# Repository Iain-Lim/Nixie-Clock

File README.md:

## Nixie_ver1
- The first board which house all the nixie tubes and the driver for it.

## Nixie2nd_ver1
- The second board which house the Arduino Nano, High Voltage Power Supply, Real-time clock, and other components
- Do note that there is a missing connection for the arduino to the ground.

## divergence_meter_ver_1_4
- Functional code for the clock/divergence meter.
- Yet to implement rolling numbers for the divegence number.

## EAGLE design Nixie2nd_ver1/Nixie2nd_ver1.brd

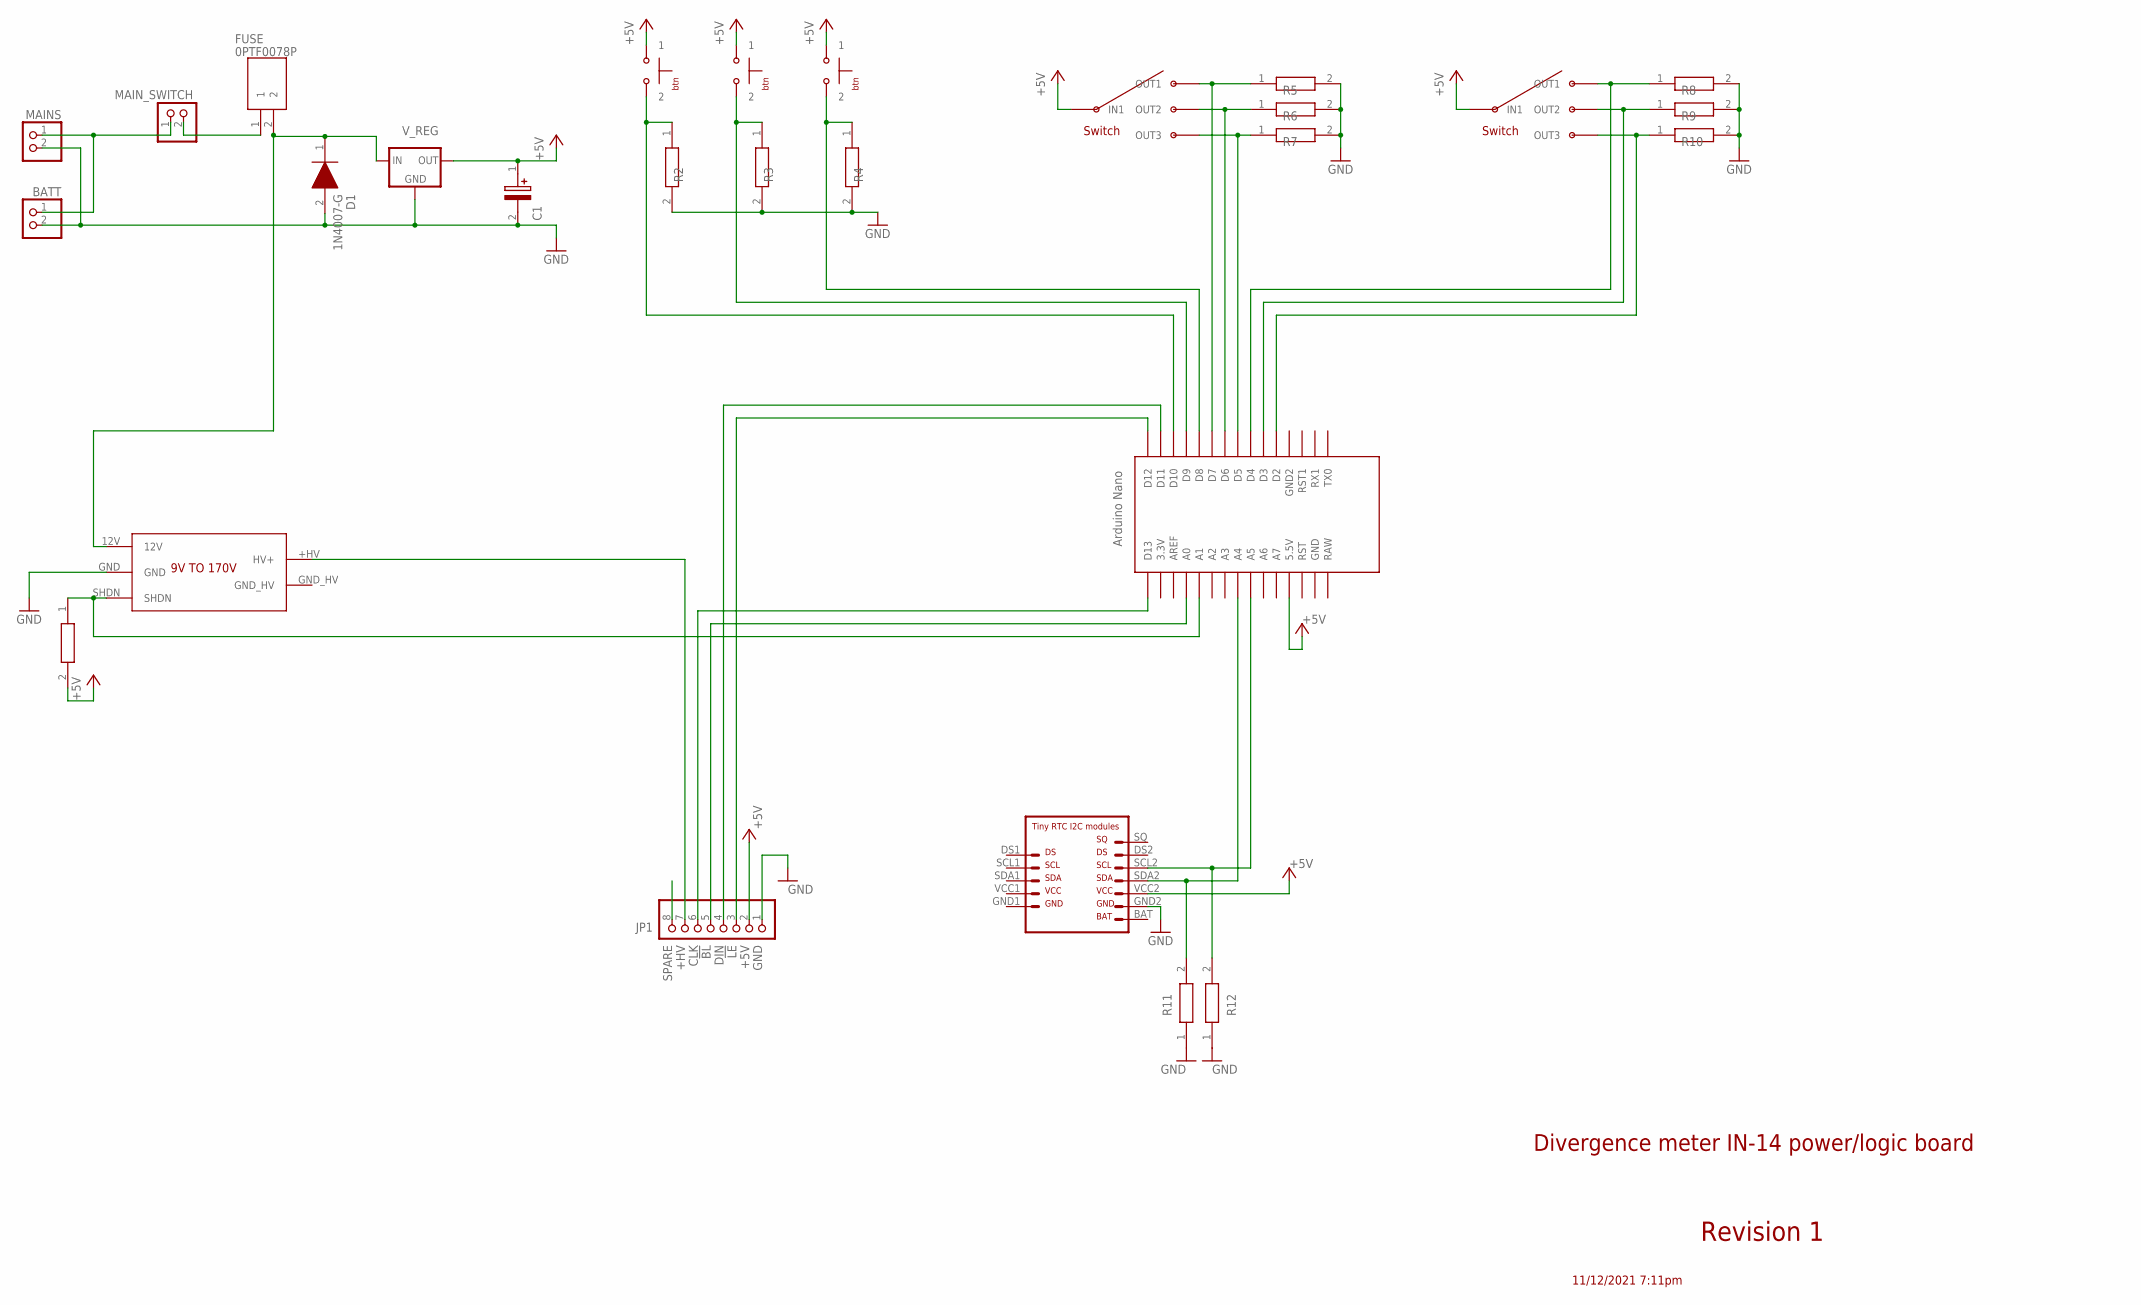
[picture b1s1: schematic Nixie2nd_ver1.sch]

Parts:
BATT: PINHD-1X2; 1X02
BTN_1, BTN_2, BTN_3: PUSH_BTN
C1: ESMG250ELL330ME11D; CAPPRD275W60D825H1300
D1: 1N4007-G; DIOAD1410W90L470D235
FUSE: 0PTF0078P
JP1: PINHD-1X8; 1X08
MAINS: PINHD-1X2; 1X02
MAIN_SWITCH: PINHD-1X2; 1X02
R1, R2, R3, R4, R5, R6, R7, R8, R9, R10, R11, R12: CR0805-FX-3303ELF; RESC2012X60N
SWITCH_1, SWITCH_2: 3WAY_SWITCH
U$1: NANO
U$2: VOLTAGE_9TO170VOLT_9TO170; VOLTAGE_9TO170
U$3: RTC
V_REG: 78XXS

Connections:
!BL: JP1.5, U$1.A0
!LE: JP1.3, U$1.D12
+5V: BTN_1.1, BTN_2.1, BTN_3.1, C1.1 (+), JP1.2, R1.2, SWITCH_1.IN1, SWITCH_2.IN1, U$1.5V (5.5V), U$3.VCC2, V_REG.OUT
+HV: JP1.7, U$2.+HV (HV+)
CLK: JP1.6, U$1.D13
DIN: JP1.4, U$1.D11
GND: BATT.2, C1.2 (-), D1.2 (A), JP1.1, MAINS.2, R2.2, R3.2, R4.2, R5.2, R6.2, R7.2, R8.2, R9.2, R10.2, R11.1, R12.1, U$2.GND, U$3.GND2, V_REG.GND
MAINS: BATT.1, MAINS.1, MAIN_SWITCH.1
MAINS_REG: D1.1 (K), FUSE.2, U$2.12V, V_REG.IN
unnamed: R5.1, SWITCH_1.OUT1, U$1.D7
unnamed: R6.1, SWITCH_1.OUT2, U$1.D6
unnamed: R7.1, SWITCH_1.OU3 (OUT3), U$1.D5
unnamed: R8.1, SWITCH_2.OUT1, U$1.D4
unnamed: R9.1, SWITCH_2.OUT2, U$1.D3
unnamed: R10.1, SWITCH_2.OU3 (OUT3), U$1.D2
unnamed: BTN_3.2, R4.1, U$1.D8
unnamed: BTN_2.2, R3.1, U$1.D9
unnamed: BTN_1.2, R2.1, U$1.D10
unnamed: FUSE.1, MAIN_SWITCH.2
SCL: R12.2, U$1.A5, U$3.SCL2
SDA: R11.2, U$1.A4, U$3.SDA2
SHDN: R1.1, U$1.A1, U$2.SHDN
SPARE: JP1.8

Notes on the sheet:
Divergence meter IN-14 power/logic board
11/12/2021 7:11pm
Revision 1

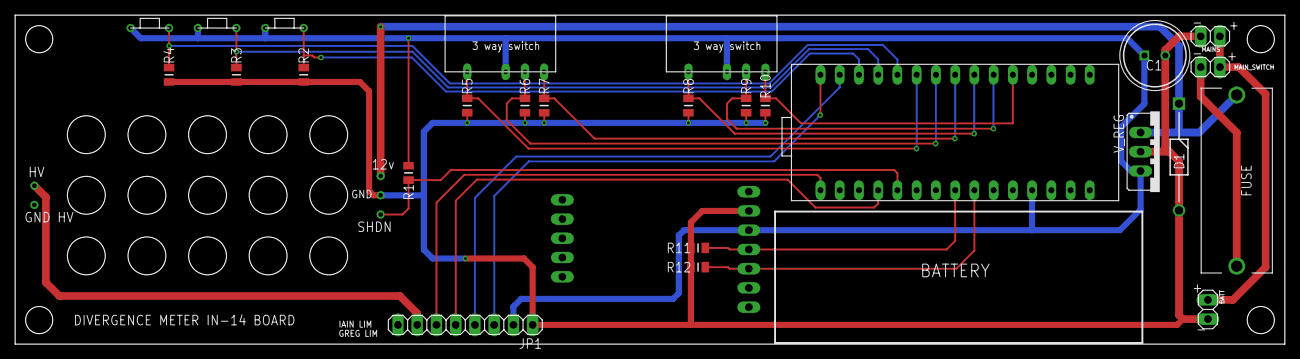
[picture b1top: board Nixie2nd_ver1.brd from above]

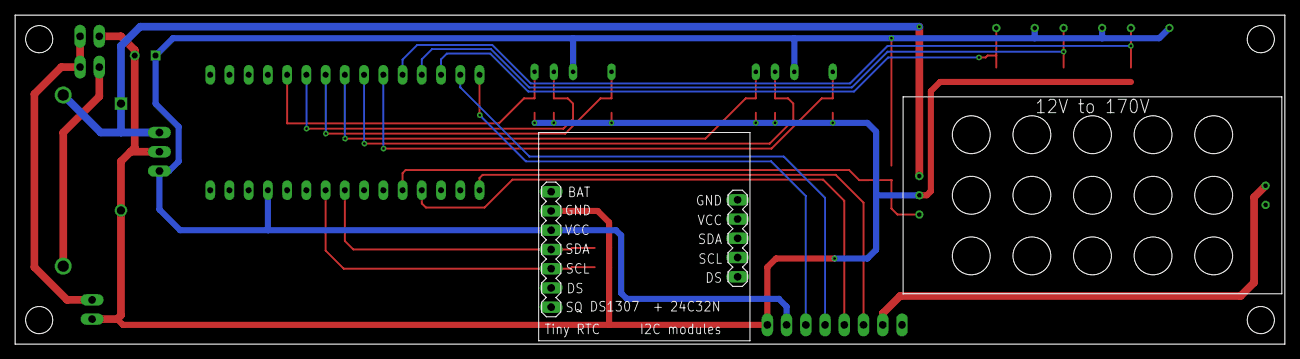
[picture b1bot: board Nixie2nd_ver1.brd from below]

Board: 2 copper layers, 167.6 x 43.4 mm, 28 parts (2 on the bottom side), 22 nets.

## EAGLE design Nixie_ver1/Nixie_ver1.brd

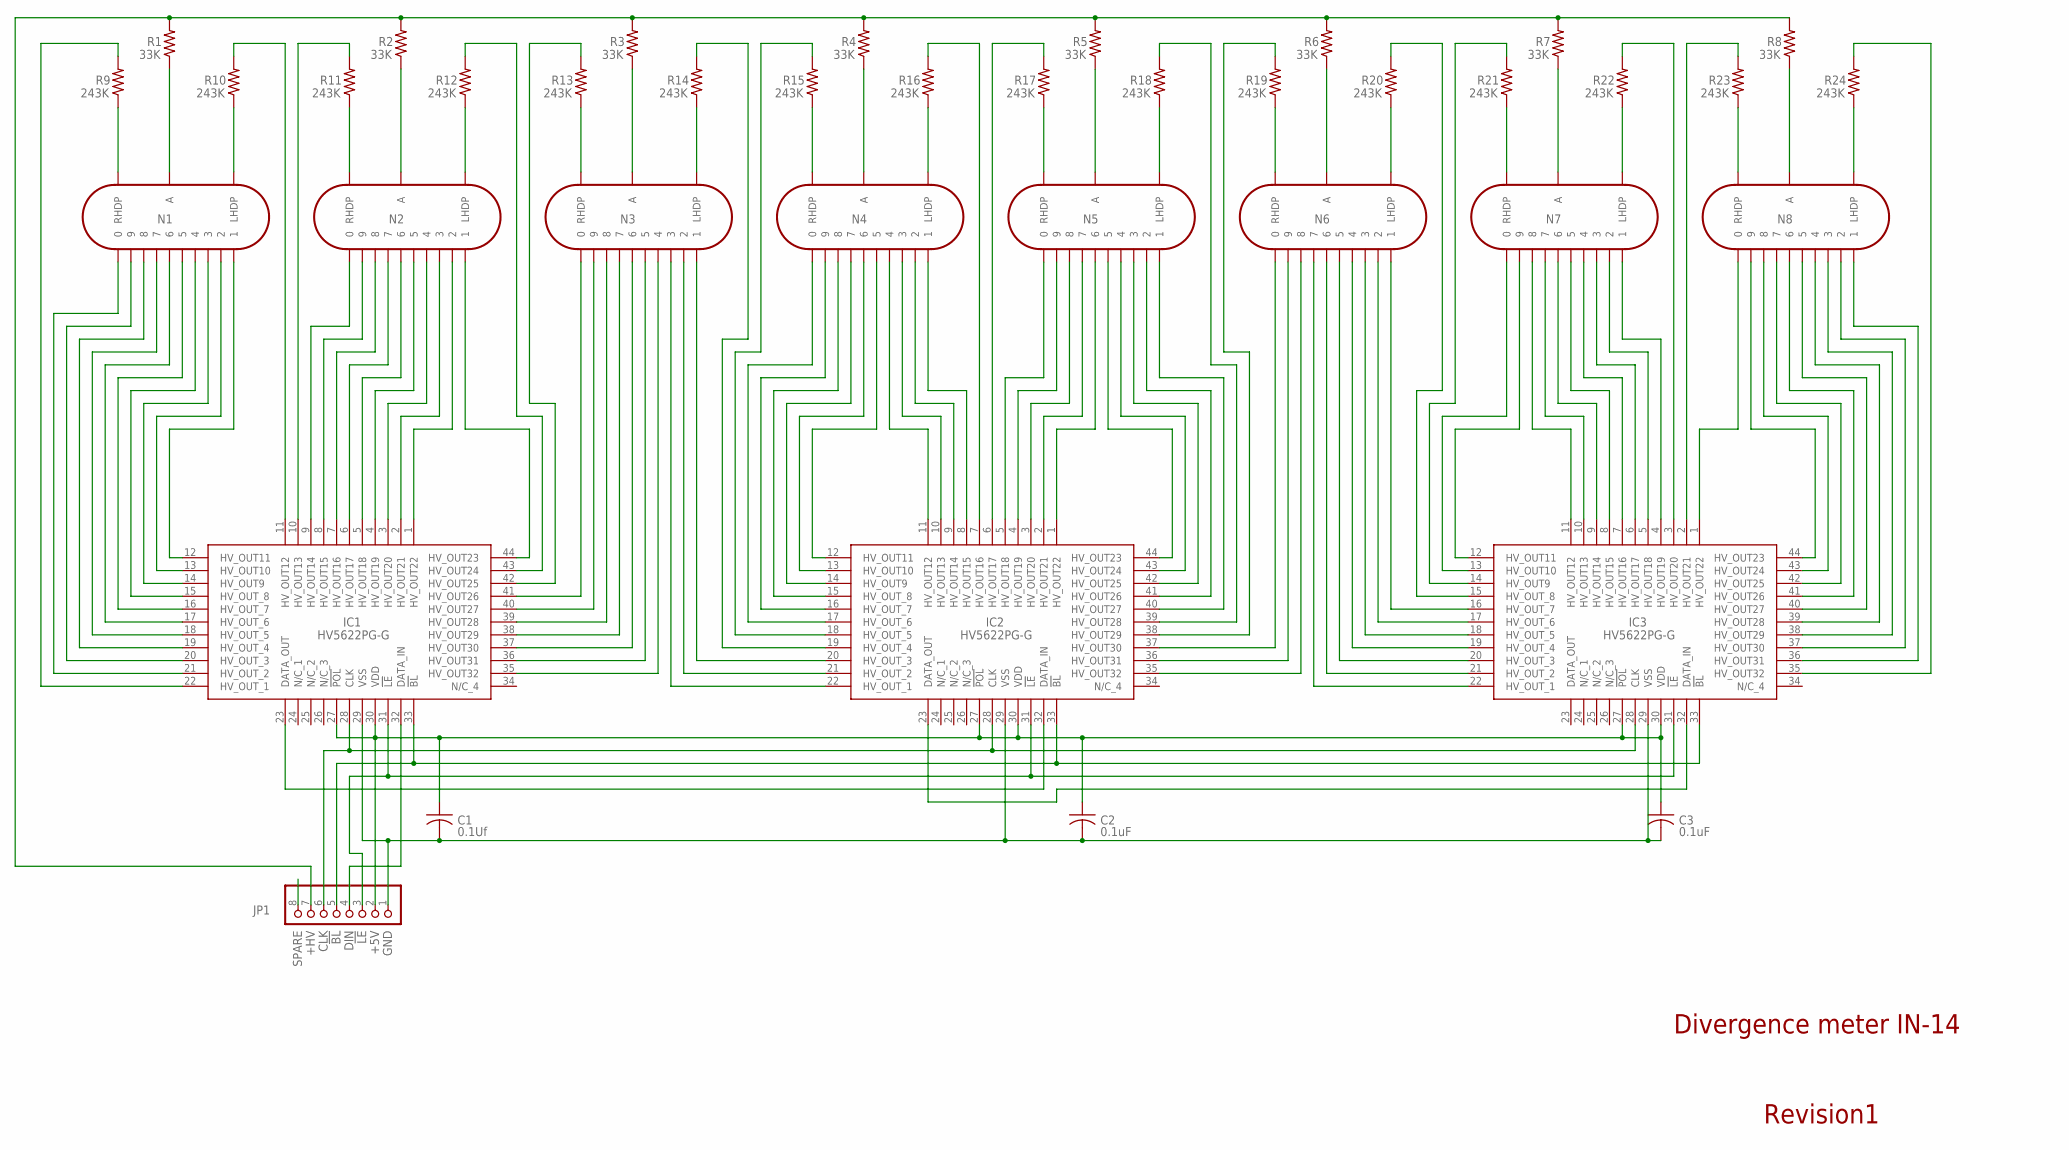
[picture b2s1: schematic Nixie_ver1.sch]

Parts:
C1: 0.1Uf; C025-024X044
C2, C3: 0.1uF; C025-024X044
IC1, IC2, IC3: HV5622PG-G; QFP80P1390X1390X235-44N
JP1: PINHD-1X8; 1X08
N1, N2, N3, N4, N5, N6, N7, N8: IN-14
R1, R2, R3, R4, R5, R6, R7, R8: 33K; 0204/7
R9, R10, R11, R12, R13, R14, R15, R16, R17, R18, R19, R20, R21, R22, R23, R24: 243K; 0204/7

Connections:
!BL!: IC1.33 (!BL), IC2.33 (!BL), IC3.33 (!BL), JP1.5
!LE!: IC1.31 (!LE), IC2.31 (!LE), IC3.31 (!LE), JP1.3
+5V: C1.1, C2.1, C3.1, IC1.27 (!POL), IC1.30 (VDD), IC2.27 (!POL), IC2.30 (VDD), IC3.27 (!POL), IC3.30 (VDD), JP1.2
+HV: JP1.7, R1.2, R2.2, R3.2, R4.2, R5.2, R6.2, R7.2, R8.2
CLK: IC1.28 (CLK), IC2.28 (CLK), IC3.28 (CLK), JP1.6
DIN: IC1.32 (DATA_IN), JP1.4
GND: C1.2, C2.2, C3.2, IC1.29 (VSS), IC2.29 (VSS), IC3.29 (VSS), JP1.1
unnamed: IC1.23 (DATA_OUT), IC2.32 (DATA_IN)
unnamed: IC2.23 (DATA_OUT), IC3.32 (DATA_IN)
unnamed: IC1.11 (HV_OUT12), R10.2
unnamed: IC1.13 (HV_OUT10), N1.2
unnamed: IC1.14 (HV_OUT9), N1.3
unnamed: IC1.15 (HV_OUT_8), N1.4
unnamed: IC1.16 (HV_OUT_7), N1.5
unnamed: IC1.17 (HV_OUT_6), N1.6
unnamed: IC1.18 (HV_OUT_5), N1.7
unnamed: IC1.19 (HV_OUT_4), N1.8
unnamed: IC1.20 (HV_OUT_3), N1.9
unnamed: IC1.12 (HV_OUT11), N1.1
unnamed: IC1.21 (HV_OUT_2), N1.0
unnamed: IC1.22 (HV_OUT_1), R9.2
unnamed: N1.RHDP, R9.1
unnamed: N1.LHDP, R10.1
unnamed: IC1.10 (HV_OUT13), R11.2
unnamed: N1.A, R1.1
unnamed: N2.RHDP, R11.1
unnamed: N2.A, R2.1
unnamed: N2.LHDP, R12.1
unnamed: IC1.9 (HV_OUT14), N2.0
unnamed: IC1.8 (HV_OUT15), N2.9
unnamed: IC1.7 (HV_OUT16), N2.8
unnamed: IC1.6 (HV_OUT17), N2.7
unnamed: IC1.5 (HV_OUT18), N2.6
unnamed: IC1.4 (HV_OUT19), N2.5
unnamed: IC1.3 (HV_OUT20), N2.4
unnamed: IC1.2 (HV_OUT21), N2.3
unnamed: IC1.1 (HV_OUT22), N2.2
unnamed: IC1.44 (HV_OUT23), N2.1
unnamed: IC1.43 (HV_OUT24), R12.2
unnamed: IC1.42 (HV_OUT25), R13.2
unnamed: N3.RHDP, R13.1
unnamed: N3.A, R3.1
unnamed: N3.LHDP, R14.1
unnamed: IC1.41 (HV_OUT26), N3.0
unnamed: IC1.40 (HV_OUT27), N3.9
unnamed: IC1.39 (HV_OUT28), N3.8
unnamed: IC1.38 (HV_OUT29), N3.7
unnamed: IC1.37 (HV_OUT30), N3.6
unnamed: IC1.36 (HV_OUT31), N3.5
unnamed: IC1.35 (HV_OUT32), N3.4
unnamed: IC2.22 (HV_OUT_1), N3.3
unnamed: IC2.21 (HV_OUT_2), N3.2
unnamed: IC2.20 (HV_OUT_3), N3.1
unnamed: IC2.19 (HV_OUT_4), R14.2
unnamed: IC2.18 (HV_OUT_5), R15.2
unnamed: N4.RHDP, R15.1
unnamed: N4.A, R4.1
unnamed: N4.LHDP, R16.1
unnamed: IC2.17 (HV_OUT_6), N4.0
unnamed: IC2.16 (HV_OUT_7), N4.9
unnamed: IC2.15 (HV_OUT_8), N4.8
unnamed: IC2.14 (HV_OUT9), N4.7
unnamed: IC2.13 (HV_OUT10), N4.6
unnamed: IC2.1 (HV_OUT22), N5.6
unnamed: IC2.11 (HV_OUT12), N4.4
unnamed: IC2.10 (HV_OUT13), N4.3
unnamed: IC2.9 (HV_OUT14), N4.2
unnamed: IC2.8 (HV_OUT15), N4.1
unnamed: IC2.7 (HV_OUT16), R16.2
unnamed: IC2.6 (HV_OUT17), R17.2
unnamed: N5.RHDP, R17.1
unnamed: N5.A, R5.1
unnamed: N5.LHDP, R18.1
unnamed: IC2.5 (HV_OUT18), N5.0
unnamed: IC2.4 (HV_OUT19), N5.9
unnamed: IC2.3 (HV_OUT20), N5.8
unnamed: IC2.2 (HV_OUT21), N5.7
unnamed: N6.RHDP, R19.1
unnamed: IC2.44 (HV_OUT23), N5.5
unnamed: IC2.43 (HV_OUT24), N5.4
unnamed: IC2.42 (HV_OUT25), N5.3
unnamed: IC2.41 (HV_OUT26), N5.2
unnamed: IC2.40 (HV_OUT27), N5.1
unnamed: IC2.39 (HV_OUT28), R18.2
unnamed: IC2.38 (HV_OUT29), R19.2
unnamed: IC2.12 (HV_OUT11), N4.5
unnamed: N6.A, R6.1
unnamed: N6.LHDP, R20.1
unnamed: N7.RHDP, R21.1
unnamed: N7.A, R7.1
unnamed: N7.LHDP, R22.1
unnamed: N8.RHDP, R23.1
unnamed: N8.A, R8.1
unnamed: N8.LHDP, R24.1
unnamed: IC2.37 (HV_OUT30), N6.0
unnamed: IC2.36 (HV_OUT31), N6.9
unnamed: IC2.35 (HV_OUT32), N6.8
unnamed: IC3.22 (HV_OUT_1), N6.7
unnamed: IC3.21 (HV_OUT_2), N6.6
unnamed: IC3.20 (HV_OUT_3), N6.5
unnamed: IC3.19 (HV_OUT_4), N6.4
unnamed: IC3.18 (HV_OUT_5), N6.3
unnamed: IC3.17 (HV_OUT_6), N6.2
unnamed: IC3.16 (HV_OUT_7), N6.1
unnamed: IC3.15 (HV_OUT_8), R20.2
unnamed: IC3.14 (HV_OUT9), R21.2
unnamed: IC3.13 (HV_OUT10), N7.0
unnamed: IC3.12 (HV_OUT11), N7.9
unnamed: IC3.11 (HV_OUT12), N7.8
unnamed: IC3.10 (HV_OUT13), N7.7
unnamed: IC3.9 (HV_OUT14), N7.6
unnamed: IC3.8 (HV_OUT15), N7.5
unnamed: IC3.7 (HV_OUT16), N7.4
unnamed: IC3.6 (HV_OUT17), N7.3
unnamed: IC3.5 (HV_OUT18), N7.2
unnamed: IC3.4 (HV_OUT19), N7.1
unnamed: IC3.3 (HV_OUT20), R22.2
unnamed: IC3.2 (HV_OUT21), R23.2
unnamed: IC3.1 (HV_OUT22), N8.0
unnamed: IC3.44 (HV_OUT23), N8.9
unnamed: IC3.43 (HV_OUT24), N8.8
unnamed: IC3.42 (HV_OUT25), N8.7
unnamed: IC3.41 (HV_OUT26), N8.6
unnamed: IC3.40 (HV_OUT27), N8.5
unnamed: IC3.39 (HV_OUT28), N8.4
unnamed: IC3.38 (HV_OUT29), N8.3
unnamed: IC3.37 (HV_OUT30), N8.2
unnamed: IC3.36 (HV_OUT31), N8.1
unnamed: IC3.35 (HV_OUT32), R24.2
SPARE: JP1.8

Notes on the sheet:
Divergence meter IN-14
Revision1

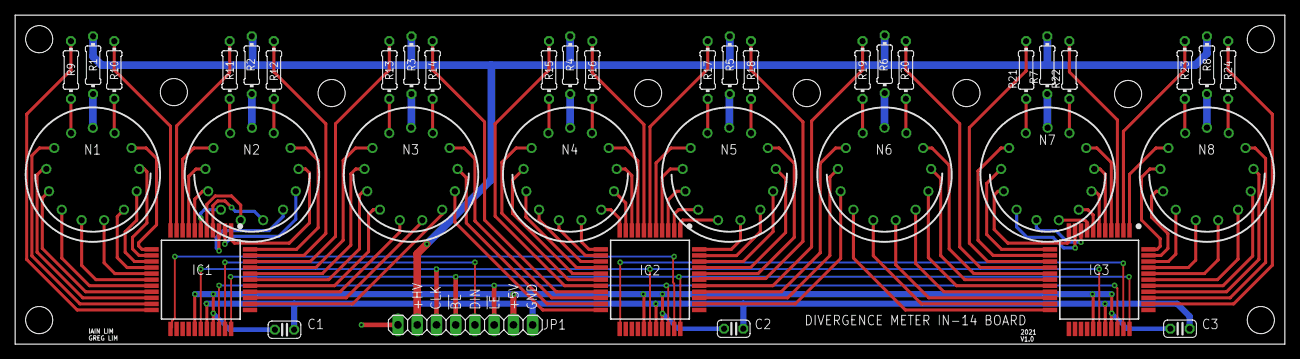
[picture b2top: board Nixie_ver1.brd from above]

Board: 2 copper layers, 167.6 x 43.4 mm, 39 parts (0 on the bottom side), 129 nets.

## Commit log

2024-03-16 README.md
